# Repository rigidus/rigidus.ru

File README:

http://rigidus.ru

My home page written on Common Lisp

Contacts:
  email:  i.am.rigidus טּ gmail.com
  jabber: rigidus@jabber.ru

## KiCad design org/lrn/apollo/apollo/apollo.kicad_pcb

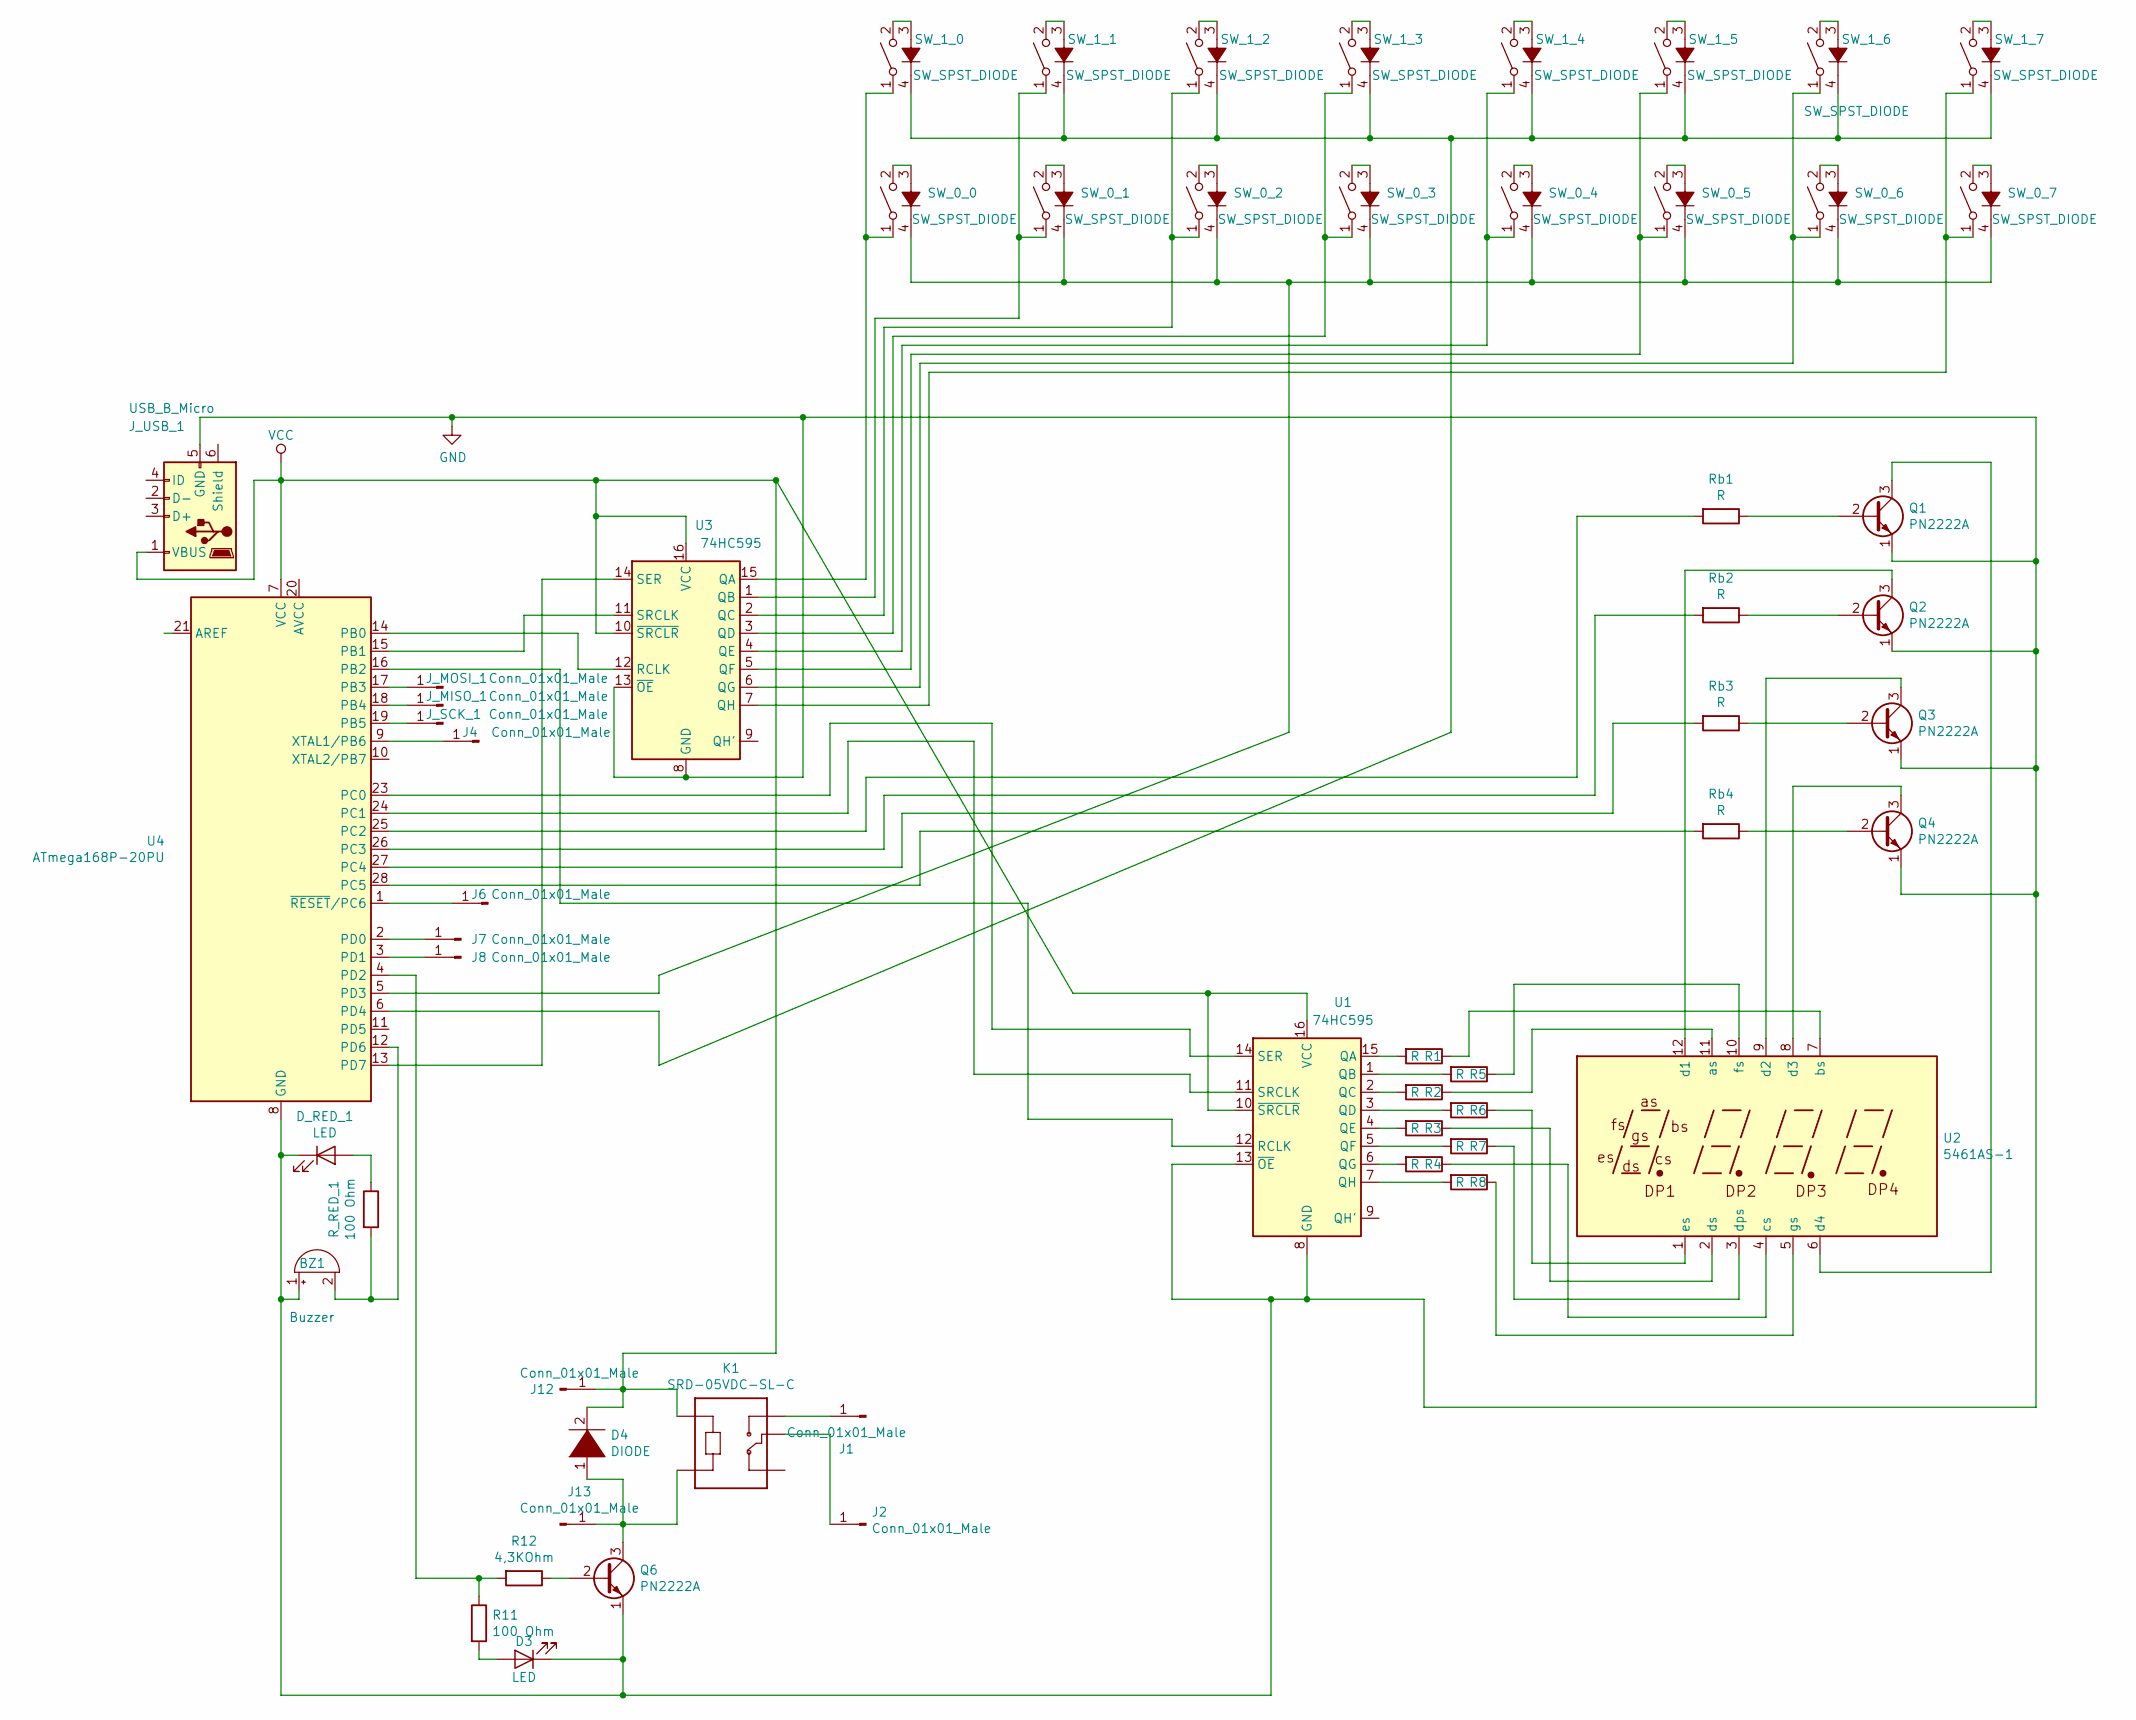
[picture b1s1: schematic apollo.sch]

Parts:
BZ1: Buzzer; Buzzer_12x9.5RM7.6
D3: LED; LED_D5.0mm_FlatTop
D4: DIODE; D_0805_2012Metric_Pad1.15x1.40mm_HandSolder
D_RED_1: LED; LED_D5.0mm_FlatTop
J1, J2: Conn_01x01_Male; PIN
J4, J6, J7, J8, J12, J13: Conn_01x01_Male; Pin_D1.0mm_L10.0mm
J_MISO_1: Conn_01x01_Male; Pin_D1.0mm_L10.0mm
J_MOSI_1: Conn_01x01_Male; Pin_D1.0mm_L10.0mm
J_SCK_1: Conn_01x01_Male; Pin_D1.0mm_L10.0mm
J_USB_1: USB_B_Micro; USB_Micro-AB_Molex_47590-0001
K1: SRD-05VDC-SL-C; RELAY_SRD-05VDC-SL-C
Q1, Q2, Q3, Q4, Q6: PN2222A; SOT-23
R1, R2, R3, R4, R5, R6, R7, R8: R; R_1206_3216Metric_Pad1.42x1.75mm_HandSolder
R11: 100 Ohm; R_1206_3216Metric_Pad1.42x1.75mm_HandSolder
R12: 4,3KOhm; R_1206_3216Metric_Pad1.42x1.75mm_HandSolder
R_RED_1: 100 Ohm; R_1206_3216Metric_Pad1.42x1.75mm_HandSolder
Rb1, Rb2, Rb3, Rb4: R; R_1206_3216Metric_Pad1.42x1.75mm_HandSolder
SW_0_0, SW_0_1, SW_0_2, SW_0_3, SW_0_4, SW_0_5, SW_0_6, SW_0_7, SW_1_0, SW_1_1, SW_1_2, SW_1_3, SW_1_4, SW_1_5, SW_1_6, SW_1_7: SW_SPST_DIODE; gateron
U1: 74HC595; DIP-16_W7.62mm
U2: 5461AS-1
U3: 74HC595; DIP-16_W7.62mm_LongPads
U4: ATmega168P-20PU; DIP-28_W7.62mm

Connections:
GND: BZ1.1 (-), D3.1 (K), D_RED_1.1 (K), J_USB_1.5 (GND), Q1.1 (E), Q2.1 (E), Q3.1 (E), Q4.1 (E), Q6.1 (E), U1.8 (GND), U1.13 (~OE), U3.8 (GND), U3.13 (~OE), U4.8 (GND), U4.22 (GND)
unnamed: BZ1.2 (+), R_RED_1.2, U4.12 (PD6)
unnamed: D3.2 (A), R11.2
unnamed: D4.1 (K), J13.1, K1.A2, Q6.3 (C)
unnamed: D_RED_1.2 (A), R_RED_1.1
unnamed: J1.1, K1.NO
unnamed: J2.1, K1.COM
unnamed: J4.1, U4.9 (XTAL1/PB6)
unnamed: J6.1, U4.1 (~RESET~/PC6)
unnamed: J7.1, U4.2 (PD0)
unnamed: J8.1, U4.3 (PD1)
unnamed: J_MISO_1.1, U4.18 (PB4)
unnamed: J_MOSI_1.1, U4.17 (PB3)
unnamed: J_SCK_1.1, U4.19 (PB5)
unnamed: Q1.2 (B), Rb1.1
unnamed: Q1.3 (C), U2.6 (d4)
unnamed: Q2.2 (B), Rb2.1
unnamed: Q2.3 (C), U2.12 (d1)
unnamed: Q3.2 (B), Rb3.1
unnamed: Q3.3 (C), U2.9 (d2)
unnamed: Q4.2 (B), Rb4.1
unnamed: Q4.3 (C), U2.8 (d3)
unnamed: Q6.2 (B), R12.1
unnamed: R1.1, U2.7 (bs)
unnamed: R1.2, U1.15 (QA)
unnamed: R2.1, U2.11 (as)
unnamed: R2.2, U1.2 (QC)
unnamed: R3.1, U2.2 (ds)
unnamed: R3.2, U1.4 (QE)
unnamed: R4.1, U2.4 (cs)
unnamed: R4.2, U1.6 (QG)
unnamed: R5.1, U2.10 (fs)
unnamed: R5.2, U1.1 (QB)
unnamed: R6.1, U2.1 (es)
unnamed: R6.2, U1.3 (QD)
unnamed: R7.1, U2.3 (dps)
unnamed: R7.2, U1.5 (QF)
unnamed: R8.1, U2.5 (gs)
unnamed: R8.2, U1.7 (QH)
unnamed: R11.1, R12.2, U4.4 (PD2)
unnamed 41: Rb1.2, U4.25 (PC2); also elsewhere on the board
unnamed: Rb2.2, U4.26 (PC3)
unnamed: Rb3.2, U4.27 (PC4)
unnamed: Rb4.2, U4.28 (PC5)
unnamed: SW_0_0.1, SW_1_0.1, U3.15 (QA)
unnamed: SW_0_0.2, SW_0_0.3 (K)
unnamed: SW_0_0.4 (A), SW_0_1.4 (A), SW_0_2.4 (A), SW_0_3.4 (A), SW_0_4.4 (A), SW_0_5.4 (A), SW_0_6.4 (A), SW_0_7.4 (A), U4.5 (PD3)
unnamed: SW_0_1.1, SW_1_1.1, U3.1 (QB)
unnamed: SW_0_1.2, SW_0_1.3 (K)
unnamed: SW_0_2.1, SW_1_2.1, U3.2 (QC)
unnamed: SW_0_2.2, SW_0_2.3 (K)
unnamed: SW_0_3.1, SW_1_3.1, U3.3 (QD)
unnamed: SW_0_3.2, SW_0_3.3 (K)
unnamed: SW_0_4.1, SW_1_4.1, U3.4 (QE)
unnamed: SW_0_4.2, SW_0_4.3 (K)
unnamed: SW_0_5.1, SW_1_5.1, U3.5 (QF)
unnamed: SW_0_5.2, SW_0_5.3 (K)
unnamed: SW_0_6.1, SW_1_6.1, U3.6 (QG)
unnamed: SW_0_6.2, SW_0_6.3 (K)
unnamed: SW_0_7.1, SW_1_7.1, U3.7 (QH)
unnamed: SW_0_7.2, SW_0_7.3 (K)
unnamed: SW_1_0.2, SW_1_0.3 (K)
unnamed: SW_1_0.4 (A), SW_1_1.4 (A), SW_1_2.4 (A), SW_1_3.4 (A), SW_1_4.4 (A), SW_1_5.4 (A), SW_1_6.4 (A), SW_1_7.4 (A), U4.6 (PD4)
unnamed: SW_1_1.2, SW_1_1.3 (K)
unnamed: SW_1_2.2, SW_1_2.3 (K)
unnamed: SW_1_3.2, SW_1_3.3 (K)
unnamed: SW_1_4.2, SW_1_4.3 (K)
unnamed: SW_1_5.2, SW_1_5.3 (K)
unnamed: SW_1_6.2, SW_1_6.3 (K)
unnamed: SW_1_7.2, SW_1_7.3 (K)
unnamed: U1.11 (SRCLK), U4.24 (PC1)
unnamed: U1.12 (RCLK), U4.16 (PB2)
unnamed: U1.14 (SER), U4.23 (PC0)
unnamed: U3.11 (SRCLK), U4.15 (PB1)
unnamed: U3.12 (RCLK), U4.14 (PB0)
unnamed: U3.14 (SER), U4.13 (PD7)
VCC: D4.2 (A), J12.1, J_USB_1.1 (VBUS), K1.A1, U1.10 (~SRCLR), U1.16 (VCC), U3.10 (~SRCLR), U3.16 (VCC), U4.7 (VCC); also elsewhere on the board

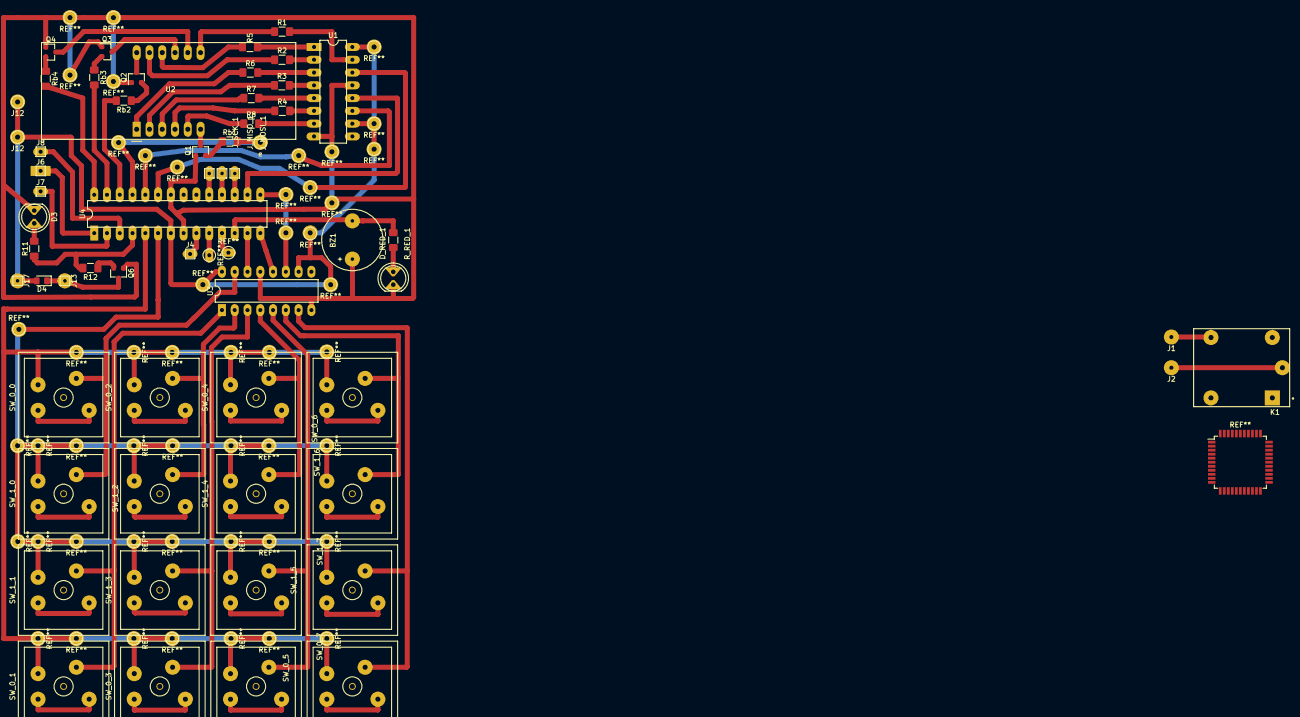
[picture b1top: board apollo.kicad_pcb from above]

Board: 2 copper layers, 59 parts (0 on the bottom side), 77 nets.

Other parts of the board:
J12#2: Conn_01x01_Male; Pin_D1.0mm_L10.0mm
J17: Conn_01x01_Male; Pin_D0.7mm_L6.5mm_W1.8mm_FlatFork
e: Pin_D1.0mm_L10.0mm

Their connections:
unnamed 41: e.1; also elsewhere on the board
VCC: J12#2.1, J17.1; also elsewhere on the board

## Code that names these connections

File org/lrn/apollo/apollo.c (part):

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#define PD 3

 /*       +-\/-+ */
 /* PC6  1|    |28  PC5 */
 /* PD0  2|    |27  PC4 */
 /* PD1  3|    |26  PC3 */
 /* PD2  4|    |25  PC2 */
 /* PD3  5|    |24  PC1 */
 /* PD4  6|    |23  PC0 */
 /* VCC  7|    |22  GND */
 /* GND  8|    |21  AREF */
 /* PB6  9|    |20  AVCC */
 /* PB7 10|    |19  PB5 */
 /* PD5 11|    |18  PB4 */
 /* PD6 12|    |17  PB3 M */
 /* PD7 13|    |16  PB2 M */
 /* PB0 14|    |15  PB1 */
 /*       +----+ */

const uint8_t pin_to_port_and_mask[] =
    {
     ((NOT_A_PORT << 4) | NOT_A_MASK), /* (0) */
     ((PC << 4) | PC6 ), /* (1) */
     ((PD << 4) | PD0 ), /* (2) */
     ((PD << 4) | PD1 ), /* (3) */
     ((PD << 4) | PD2 ), /* (4) */
     ((PD << 4) | PD3 ), /* (5) */
     ((PD << 4) | PD4 ), /* (6) */
     ((NOT_A_PORT << 4) | NOT_A_MASK), /* VCC (7) */
     ((NOT_A_PORT << 4) | NOT_A_MASK), /* GND (8) */
     ((PB << 4) | PB6 ), /* (9) */
     ((PB << 4) | PB7 ), /* (10) */
     ((PD << 4) | PD5 ), /* (11) */
     ((PD << 4) | PD6 ), /* (12) */
     ((PD << 4) | PD7 ), /* (13) */
     ((PB << 4) | PB0 ), /* (14) */
     /* --- */
     ((PB << 4) | PB1 ), /* (15) */
     ((PB << 4) | PB2 ), /* (16) */
     ((PB << 4) | PB3 ), /* (17) */
     ((PB << 4) | PB4 ), /* (18) */
     ((PB << 4) | PB5 ), /* (19) */
     ((NOT_A_PORT << 4) | NOT_A_MASK), /* AVCC (20) */
     ((NOT_A_PORT << 4) | NOT_A_MASK), /* AREF (21) */
     ((NOT_A_PORT << 4) | NOT_A_MASK), /* GND (22) */
     ((PC << 4) | PC0 ), /* (23) */
     ((PC << 4) | PC1 ), /* (24) */
     ((PC << 4) | PC2 ), /* (25) */
     ((PC << 4) | PC3 ), /* (26) */
     ((PC << 4) | PC4 ), /* (27) */
     ((PC << 4) | PC5 ), /* (28) */
    };


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
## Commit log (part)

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2019-01-26 mycoin
2019-01-27 serialization
2019-01-29 verifyer todo
2019-02-09 motochoice
2019-02-09 grammar fix
2019-04-02 delay switch added
2019-04-02 delay-switch: button added
2019-04-02 delay_switch: debuggin script
2019-04-03 delay_switch & pass | debugging
2019-04-03 delay_switch documentation
2019-04-04 delay_switch: switching on bnt pressed
2019-04-04 delay_switch literate programm
2019-04-06 delay switch: uploaded to Attiny13
2019-04-06 delay_switch: C-level & Makefile
2019-04-07 delay_switch: 2 ctrl
2019-04-07 delay_switch: minimal asm code
2019-04-08 delay_switch: asm divide
2019-04-10 blnker
2019-04-10 dbg2
2019-04-10 delay_switch5.S int problem
2019-04-10 irq problem
2019-04-11 extended avr disasm hex and bin in Makefile
2019-04-11 point of
2019-04-11 vectors solved
2019-04-11 delay_switch2 : win!
2019-04-14 delay_switch: asm-level docs
2019-04-15 guide to linker
2019-08-12 tesseract in hh + delay_switch
2019-08-12 x-screenshot
2019-08-13 fix for teasers
2019-08-13 hh base explains
2019-08-13 hh : vac fix
2019-08-16 hh: fix
2019-08-19 c-variant blink with Makefile for attiny2313
2019-08-19 assembler-variant blink with Makefile fix for attiny2313
2019-08-26 .gitattributes
2019-08-31 prj/pass added
2019-08-31 reexport
2019-08-31 pass.export
2019-09-07 snapshot.org
2019-09-07 snapshot binarization
2019-09-07 snapshot: binarization with threshold
2019-09-07 snapshot: image-scan
2019-09-07 snapshot: set-red
2019-09-07 cell segmentation: step 1
2019-09-07 bounding box
2019-09-08 little increase speed
2019-09-08 snapshot: vectorization and saving grayscale png
2019-09-08 binarization test changed
2019-09-09 fast cellular automata
2019-09-09 fix naming
2019-09-10 b2313.S
2019-09-10 .S refactor
2019-09-10 scaler
2019-09-11 2313 input+
2019-09-13 snapshot: append-image
2019-09-14 snapshot: new load-image
2019-09-14 snapshot: get rid vectorization
2019-09-14 snapshot: binarization fix
2019-09-14 snapshot: append-image refactored
2019-09-17 snapshot: new version of append-image
2019-09-17 snapshot: append-image with grayscale
2019-09-17 snapshot: append-xor added
2019-09-17 snapshot: xor analysis
2019-09-17 snapshot: bit magic
2019-09-18 del www/*; 2313: explain timers
2019-09-18 export by right version of orgmode
2019-09-21 delay_switch: stable blinking
2019-09-21 b:add pb3
2019-09-21 noweb-ref
2019-09-21 delay-switch: timer0 ctc mode works
2019-09-22 delay_switch: independence timers
2019-09-23 delay_switch: IR
2019-09-24 delay_switch: compiler
2019-09-24 bugfix
2019-09-25 delay_switch: refactor compiler start
2019-09-25 delay_switch: refactoring in progress
2019-09-25 delay_switch: rule_when
2019-09-25 delay: case
2019-09-25 delay: fix dependency
2019-09-25 delay: fix block params, avoid reads
2019-09-26 delay: asmcode generated
2019-09-26 delay: bugfixes
2019-09-26 delay: microfix
2019-09-26 delay: many fixes
2019-09-26 delay: many fixes 2
2019-09-27 delay: case-of compilation refactored
2019-09-27 delay: case works
2019-09-28 delay: commens for asm generated code
2019-09-28 delay: schematic
2019-09-28 delay: add PB3
2019-09-28 delay: debugging
2019-09-29 delay: yellow added
2019-09-29 delay: one button works
2019-09-30 delay: save SREG in interrupt routine
2019-10-01 delay: remove unused eq3 op
2019-10-02 delay: dbg
2019-10-02 delay: fix
2019-10-02 delay: optimization leds
2019-10-04 delay: broken
2019-10-04 delay: fix end_press_handler
2019-10-04 delay: gen-get-btn-signal
2019-10-04 delay: indirect NEW
2019-10-04 delay: all indirect access
2019-10-04 delay: optimize codegen
2019-10-04 delay: prospect
2019-10-04 delay: PREV_STATE added
2019-10-06 delay :zero offset in case jmp table
2019-10-06 delay: avoid zero in case
2019-10-06 delay: it worksmake asmflash!
2019-10-06 delay: x4
2019-10-06 delay: grammar fixes
2019-10-08 kaspersky-disas added
2019-10-09 asm: hellofile.S added
2019-10-20 asm hellofile refactoring
2019-10-26 16bit compare in DELAY and change Makefile
2019-10-26 fix Makefile
2019-10-26 delay 16bit works
2019-10-27 delay: chains works
2019-10-27 refactoring
2019-10-27 timer broken
2019-10-27 delay: it works, but no sound
2019-10-27 delay:works wth sound
2019-10-27 microfix
2019-10-28 delay: scheme refactoring pins
2019-10-28 delay: schematic microfix
2019-10-28 delay: move green from :pb4 to :pb1
2019-10-28 delay: signal=sirena
2019-10-28 delay: signal fix
2019-10-28 delay: fix sound bug
2019-10-28 delay: schematic fix
2019-10-28 delay: port init & macro for on/off led
2019-10-28 delay: fix port initialization
2019-10-29 delay: led indication for alarm mode is works
2019-10-29 delay: tangle block dependency
2019-10-31 delay: debug-fix non-initialized SRAM vars
2019-11-04 servo added
2019-11-04 timer abjusting
2019-11-04 servo fix
2019-11-04 servo: scheme updated
2019-11-04 servo: scheme microfix
2019-11-05 l293d datasheet added
2019-11-18 resource stm32 added
2019-11-19 TAOCP-4A added
2019-11-23 survey: timers
2019-11-23 survey: org blocks separated
2019-11-23 survey: plan & frp-model
2019-11-23 survey: packer save to file
2019-11-23 survey: with binarization
2019-11-23 survey: not debugged pack
2019-11-25 survey: optimize pack and unpack
2019-11-25 survey: base64 and upload works but need refactoring
2019-11-26 survey: diffs
2019-11-26 survey: micro refactoring
2019-11-27 survey: separate making png sequence and saving
2019-11-27 survey: enc/dec works
2019-11-28 survey: command receiving
2019-11-28 survey: send code
2019-11-29 suvey: code improvements
2019-11-29 survey: upload
2019-11-29 survey: upload and report
2019-11-29 survey: revert timers (need for command processing)
2019-11-29 survey: fix upload json error
2019-11-29 survey: pak test
2019-11-29 survey: unpack proc works
2019-11-29 survey: throw err
2019-12-01 survey:supervisor added
2019-12-01 survey: watchdog
2019-12-02 survey: command execution without encryption
2019-12-02 survey: broken build
2019-12-02 survey: fix
2019-12-03 syrvey: global refactoring
2019-12-03 survey: supervisor improved
2019-12-03 survey: correct behavior when upload failure
2019-12-03 survey: operator started
2019-12-03 survey: plantuml documentation for supervisor actions
2019-12-04 survey: rule-based operator's dispatcher
2019-12-04 survey: replace simple lock to with-recursive-lock
2019-12-04 survey: ignore errors for sendmsg and todo for timeout locking
2019-12-06 survey: encode/decode cmd
2019-12-06 survey: update
2019-12-06 survey: update procedure explain
2019-12-08 syrvey: many improvements
2019-12-09 survey: remoute gui
2019-12-12 survey: supervisor way in operator's function
2019-12-13 resourcess: add lisp book
2019-12-13 survey: async processing
2019-12-13 survey: async works
2019-12-14 survey: autodowload works
2019-12-14 syrvey: commands for request and answer
2020-01-10 survey: channel tangling
2020-01-16 insolar
2020-02-16 survey updated
2020-04-02 cookbook added
2020-04-12 saving princess
2020-04-21 snapshot: simplyfied cell gramma separation algorypthm
2020-05-28 snapshot: draw center
2020-05-28 snapshot: nearest-neighbour union experiment
2020-05-29 snapshot: draw line
2020-05-29 snapshot: broken gif
2020-05-30 snapshot: gif debug for bounding boxes
2020-05-30 snapshot: format fix
2020-06-19 apollo.org added
2020-07-24 apollo: 7-segment pinout
2020-07-29 snapshot: animate gif helper function
2020-08-16 republish all
2020-08-16 replace repo to src
2020-08-20 appollo directory
2020-08-20 apollo pcb
2020-08-20 apollo pcb fix: wrong transistor footprint
2020-08-21 apollo: pcb compact
2020-08-21 apollo: test.ino
2020-09-04 keyb
2020-09-04 apollo: change pins
2020-09-04 apollo: draft ino
2020-09-04 apollo hexout
2020-09-04 apollo time slots
2020-09-05 apollo: interactive
2020-09-05 apollo: fix case break bug
2020-09-06 apollo: it's work
2020-09-06 apollo: send zero from cols to rows in keyb polling
2020-09-06 apollo: fast return from keyb polling
2020-09-07 apollo: keyboard shift register works
2020-09-08 apollo: keyb driver: additional track-vias
2020-09-09 apollo: keyb scan doc
2020-09-10 apollo: attiny2313 as MCU
2020-09-14 apollo: 2313 asm
2020-09-14 apollo: blink in c variant
2020-09-15 apollo: c-variant data block
2020-09-16 apollo: timer WIP
2020-09-16 apollo: one second timer in CTC mode
2020-09-17 apollo: change mmcu=atmega168
2020-09-18 apollo: display works w/o timing
2020-09-18 apollo: update schematic (draft)
2020-09-18 apollo: schematic updated
2020-09-19 apollo: bit magic optimization on digitalWrite
2020-09-19 apollo: pcm updated
2020-09-19 apollo: pcb-bak removed
2020-09-19 apollo: pcb optimizing
2020-09-19 apollo: timer setting explain upgraded
2020-09-19 apollo: greeting and countdown works
2020-09-19 apollo: timer2 enabled for blinking
2020-09-19 apollo: pin_read/write will return error value
2020-09-20 apollo: keyb dbg wip
2020-09-20 apollo: dbg
2020-09-20 apollo: dbg 2
2020-09-20 apollo: bcd localization
2020-09-20 apollo: heisenbug
2020-09-20 apollo: pcb additions
2020-09-21 apollo:keyb read with dbg out
2020-09-21 apollo: keyb works with debug out
2020-09-22 apollo: roadmap added
2020-09-24 apollo: free timer_1
2020-09-25 apollo: roadmap updated
2020-09-25 apollo: beep programmed
2020-09-25 apollo: beep schematic
2020-09-26 apollo: conditional compilation
2020-09-27 apollo: debug - in progress
2020-09-27 apollo: eeprom & beeper works
2020-09-27 apollo: add beep LED signalization to scheme
2020-09-27 apollo: add R_LED for LED beeper in scheme
2020-09-28 apollo schematic: remove test contact pins
2020-09-29 apollo: relay_1 works properly in all modes
2020-09-29 apollo: update schematic and pcb for relay_1
2020-09-30 apollo: pcb updated
2020-09-30 apollo: pcb improvements - separate two part of functuionality: display and control
2020-10-01 apollo: global refactoring for schematic and add relay_2
2020-10-01 apollo: remove relays (connectors instead)
2020-10-01 apollo:pcb improvement
2020-10-02 apollo: checkpoint
2020-10-03 apollo: read from flash by press '/'
2020-10-12 apollo:scheme micro usb connector for vcc and gnd
2020-11-05 apollo: fix gnd track and prepare to use 9 pin
2020-11-05 apollo: servo control
2020-11-07 apollo: gateron footprint added
2020-11-07 apollo: keybard added
2020-11-07 apollo: keubord linked in pcb
2020-11-07 apollo: keyboard pcb regularization
2020-11-08 replace R100-Ohm resistors for 7-segment to smd
2020-11-09 apollo: pcb regularization
2020-11-09 apollo: pcb compactification and optimization
2020-11-10 apollo: pcb compactify
2020-11-13 apollo: pcb big pads
2020-11-13 apollo:pcb optimization
2020-11-14 apollo: pcb first release
2020-11-18 apollo: new keyb
2020-11-18 apollo: pcb fix
2020-11-18 apollo: new keyb_scan() with ring buffer
2020-11-20 apollo: add Relay_2 on/off
2020-11-21 netlist optimization
2020-11-21 apollo: change relay pin from 10 to 4
2020-11-21 apollo: pcb improvements
2020-11-21 apollo: one relay
2020-11-21 apollo: pcb checkpoint
2020-11-22 apollo: pcb checkpoint 2
2020-11-22 apollo: little pcb tuning
2020-11-23 v0.03
2020-11-23 apollo: fix single relay
2020-11-25 apollo: add relay to schematic and pcb
2020-11-30 apollo: makefile .PHONY
2020-12-16 rack: started
2021-01-17 new article - so
2021-01-17 current
2021-01-17 relo: pic of plt.got
2021-01-17 relo fix
2021-01-17 history-of-calling-conventions added
2021-02-07 fix forth-1
2021-02-13 doc:why-i-still-lisp-and-you-should-too added
2021-04-01 noweb fix
2021-09-02 rack updated
2021-09-02 rack updated 2
2021-09-02 rack updated 3
2021-09-02 rack updated 4
2021-09-02 rack updated 5 + pic.png
2022-10-26 fix forth64 litstring missing
2022-10-27 plainforth
2022-10-27 Makefile updated
2022-11-01 WIP: _WORD
2022-11-01 minimal working plain forth
2022-11-01 wordsize fix
2022-11-02 wip: [todo:here]
2022-11-04 code_INTERPRET works
2022-11-04 working org
2022-11-08 gdbinit & relaforth basics
2022-11-08 unuset files removed
2022-11-09 emit debugged
2022-11-09 simple_primitives, mod, comparission debugged
2022-11-09 words for memory fetch and store debugged
2022-11-09 dspfetch & dspstore :: debugged
2022-11-09 TELL word
2022-11-09 LITSTRING, CHAR words debugged
2022-11-09 debugged: Compilation words: LBRAC/RBRAC, HIDDEN, CREATE, COLON, SEMICOLON
2022-11-09 Other: TDFA, IMMEDIATE, TICK, EXECUTE, DODOES, ARGV, ARGC, other consts, extended syscalls
